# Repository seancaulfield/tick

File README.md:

tick
====

Terribly Illuminated Chronology Keeper

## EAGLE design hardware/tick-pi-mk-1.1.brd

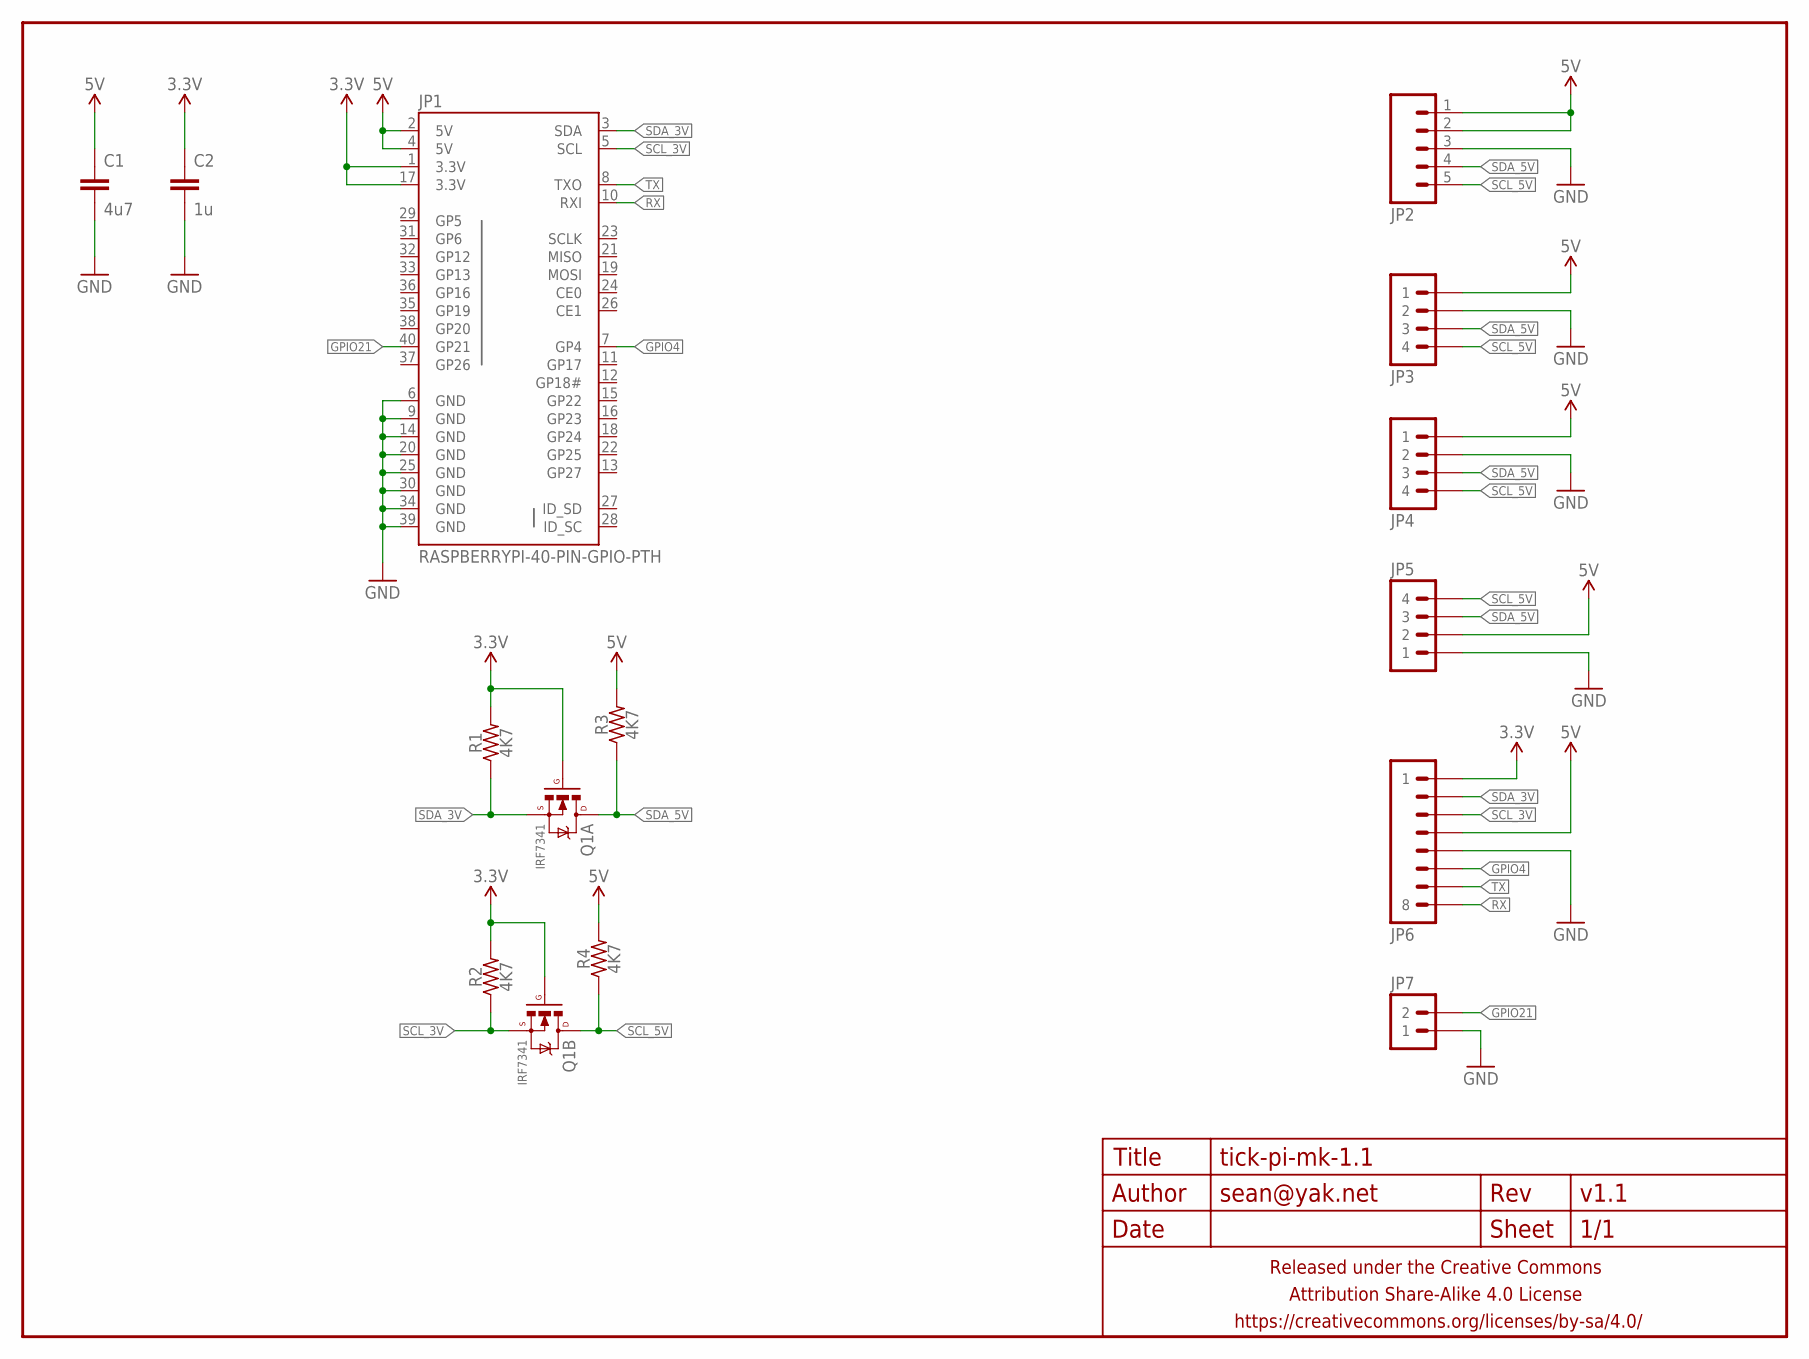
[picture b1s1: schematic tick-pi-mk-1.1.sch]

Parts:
C1: 4u7; C0805-TIGHTER
C2: 1u; C0603-TIGHTER
FRAME1: FRAME-LETTERNO_PACKAGE; DUMMY
JP1: RASPBERRYPI-40-PIN-GPIO-PTH; 2X20_PTH
JP2: M05PTH-CENTERED-RA-FEMALE; 1X05_PTH_CENTERED_RA_FEMALE
JP3, JP4, JP5: M04PTH; 1X04-PTH-VERT
JP6: M081X08; 1X08
JP7: M02PTH-CENTERED; 1X02-CENTER
Q1: IRF7341; SO08
R1, R2, R3, R4: 4K7; R0603

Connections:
3.3V: C2.1, JP1.1 (3.3V), JP1.17 (3.3V), JP6.1, Q1.2 (G), Q1.4 (G), R1.2, R2.2
5V: C1.1, JP1.2 (5V), JP1.4 (5V), JP2.1, JP2.2, JP3.1, JP4.1, JP5.2, JP6.4, R3.2, R4.2
GND: C1.2, C2.2, JP1.6 (GND), JP1.9 (GND), JP1.14 (GND), JP1.20 (GND), JP1.25 (GND), JP1.30 (GND), JP1.34 (GND), JP1.39 (GND), JP2.3, JP3.2, JP4.2, JP5.1, JP6.5, JP7.1
GPIO4: JP1.7 (GP4), JP6.6
GPIO21: JP1.40 (GP21), JP7.2
RX: JP1.10 (RXI), JP6.8
SCL_3V: JP1.5 (SCL), JP6.3, Q1.3 (S), R2.1
SCL_5V: JP2.5, JP3.4, JP4.4, JP5.4, Q1.5 (D), Q1.6 (D), R4.1
SDA_3V: JP1.3 (SDA), JP6.2, Q1.1 (S), R1.1
SDA_5V: JP2.4, JP3.3, JP4.3, JP5.3, Q1.7 (D), Q1.8 (D), R3.1
TX: JP1.8 (TXO), JP6.7

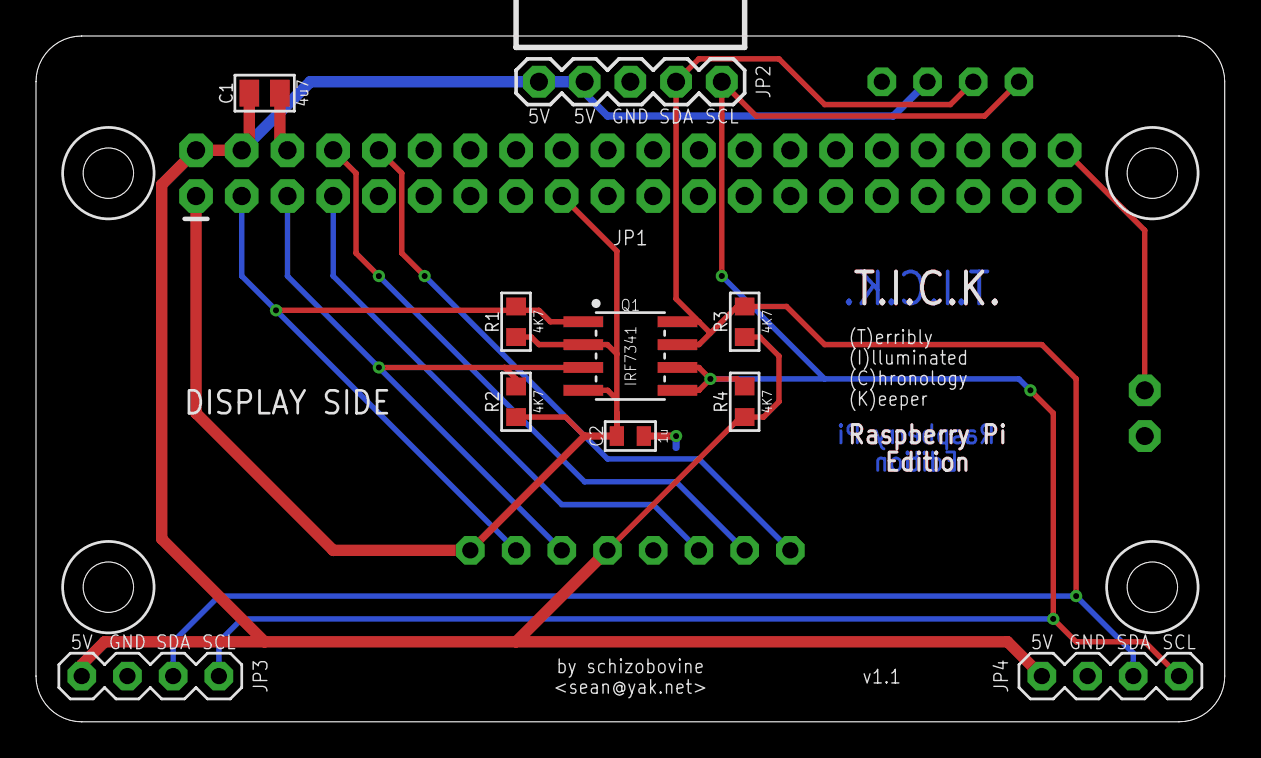
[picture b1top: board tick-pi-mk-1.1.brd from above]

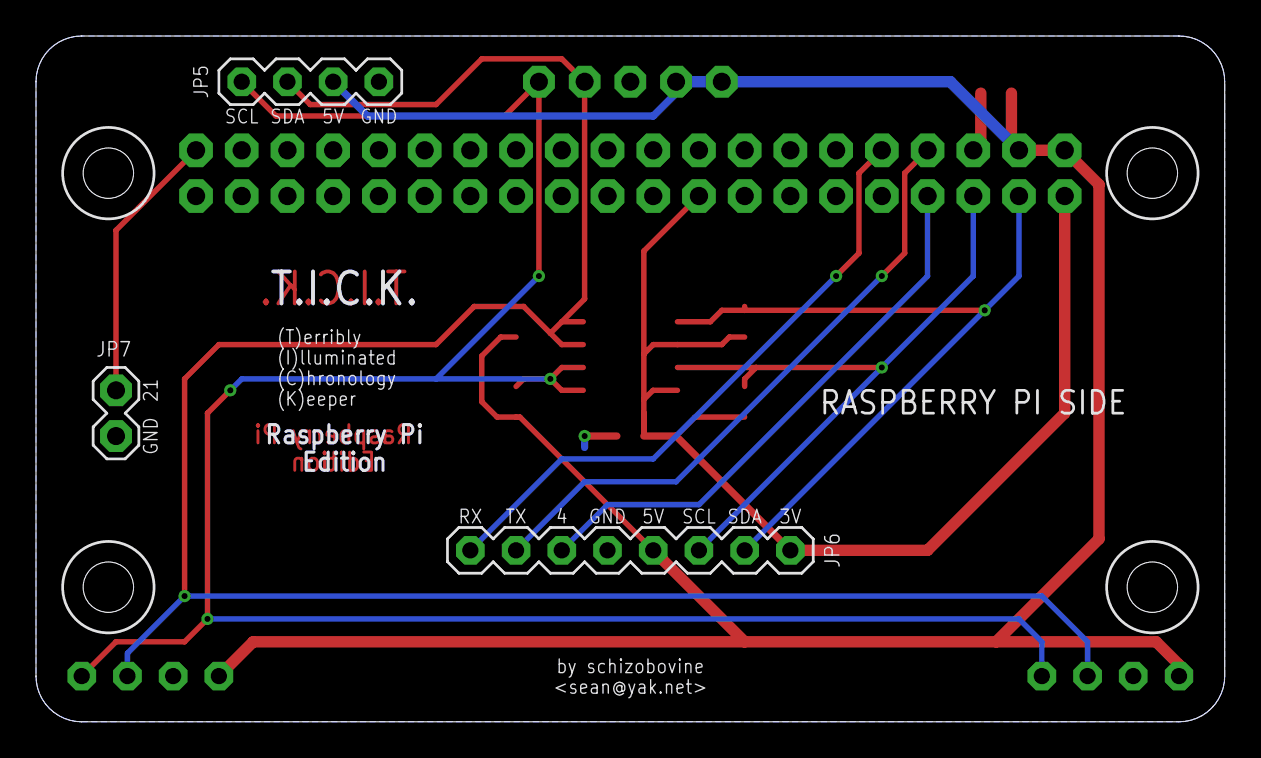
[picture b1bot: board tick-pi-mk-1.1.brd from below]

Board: 2 copper layers, 66.0 x 38.1 mm, 15 parts (3 on the bottom side), 11 nets.

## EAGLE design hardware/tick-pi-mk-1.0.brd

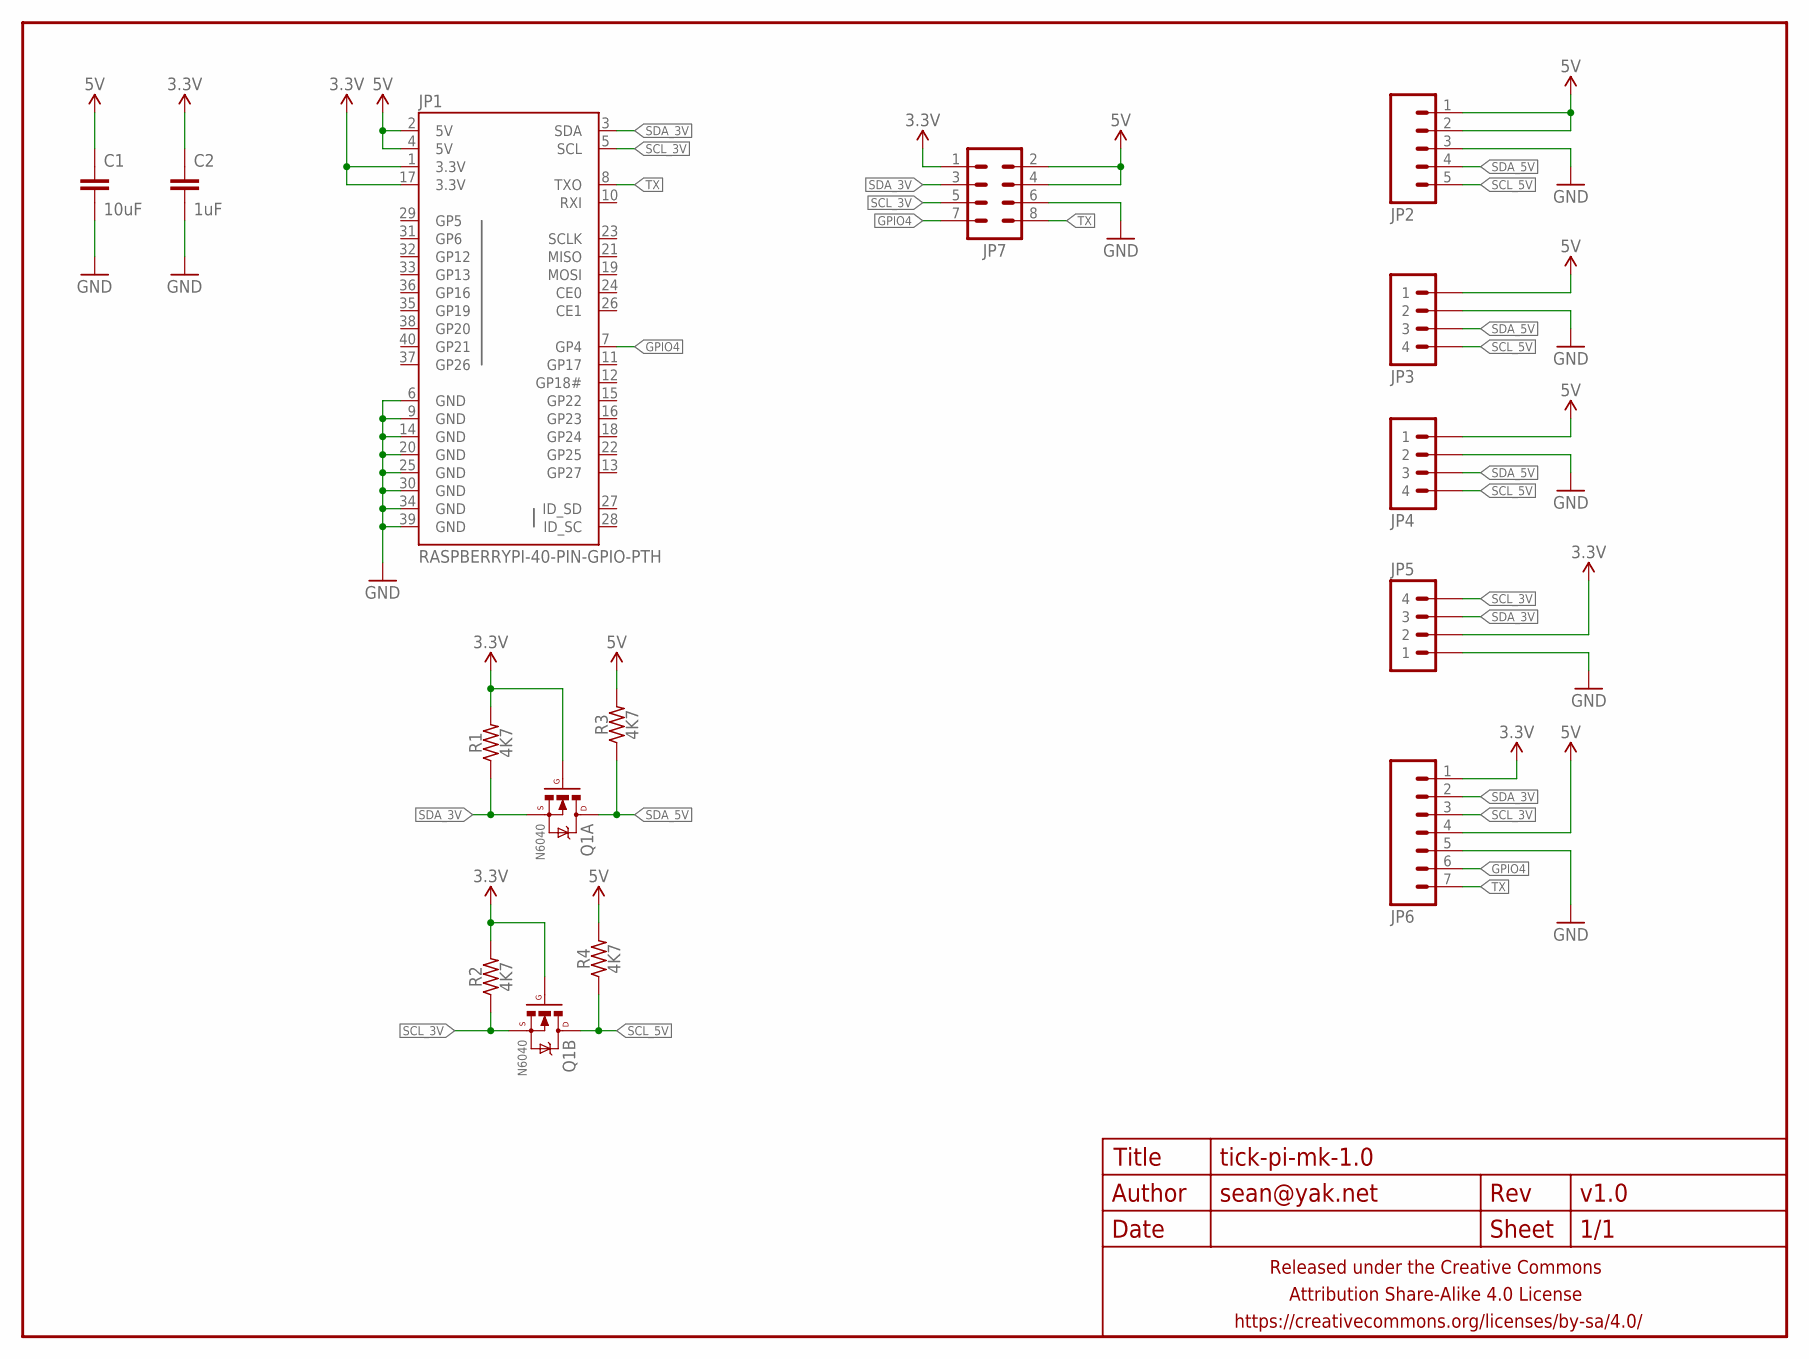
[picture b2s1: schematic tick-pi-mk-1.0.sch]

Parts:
C1: 10uF; C0805-TIGHTER
C2: 1uF; C0805-TIGHTER
FRAME1: FRAME-LETTERNO_PACKAGE; DUMMY
JP1: RASPBERRYPI-40-PIN-GPIO-PTH; 2X20_PTH
JP2: M05PTH-CENTERED-RA-FEMALE; 1X05_PTH_CENTERED_RA_FEMALE
JP3, JP4, JP5: M04PTH; 1X04-PTH-VERT
JP6: M07; 1X07
JP7: M04X2PTH; 2X4_PTH
Q1: N6040; SO08
R1, R2, R3, R4: 4K7; R0603

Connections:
3.3V: C2.1, JP1.1 (3.3V), JP1.17 (3.3V), JP5.2, JP6.1, JP7.1, Q1.2 (G), Q1.4 (G), R1.2, R2.2
5V: C1.1, JP1.2 (5V), JP1.4 (5V), JP2.1, JP2.2, JP3.1, JP4.1, JP6.4, JP7.2, JP7.4, R3.2, R4.2
GND: C1.2, C2.2, JP1.6 (GND), JP1.9 (GND), JP1.14 (GND), JP1.20 (GND), JP1.25 (GND), JP1.30 (GND), JP1.34 (GND), JP1.39 (GND), JP2.3, JP3.2, JP4.2, JP5.1, JP6.5, JP7.6
GPIO4: JP1.7 (GP4), JP6.6, JP7.7
SCL_3V: JP1.5 (SCL), JP5.4, JP6.3, JP7.5, Q1.3 (S), R2.1
SCL_5V: JP2.5, JP3.4, JP4.4, Q1.5 (D), Q1.6 (D), R4.1
SDA_3V: JP1.3 (SDA), JP5.3, JP6.2, JP7.3, Q1.1 (S), R1.1
SDA_5V: JP2.4, JP3.3, JP4.3, Q1.7 (D), Q1.8 (D), R3.1
TX: JP1.8 (TXO), JP6.7, JP7.8

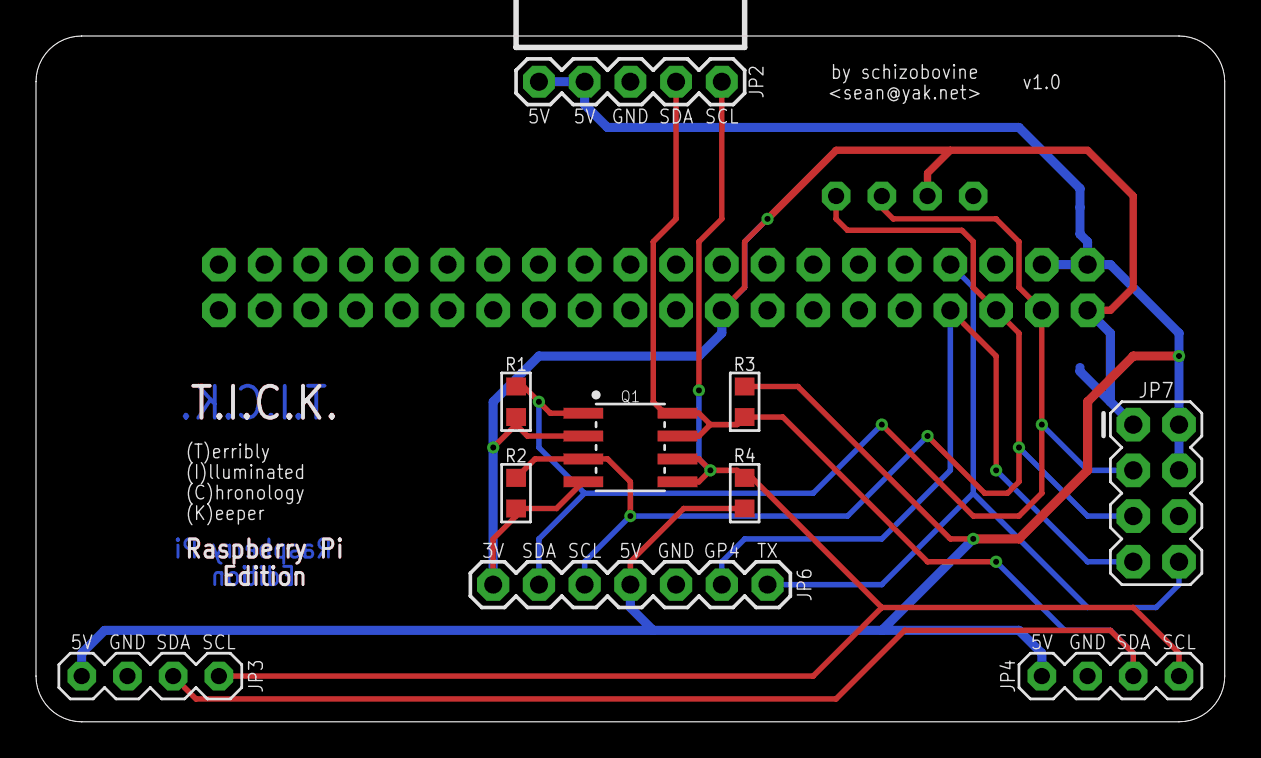
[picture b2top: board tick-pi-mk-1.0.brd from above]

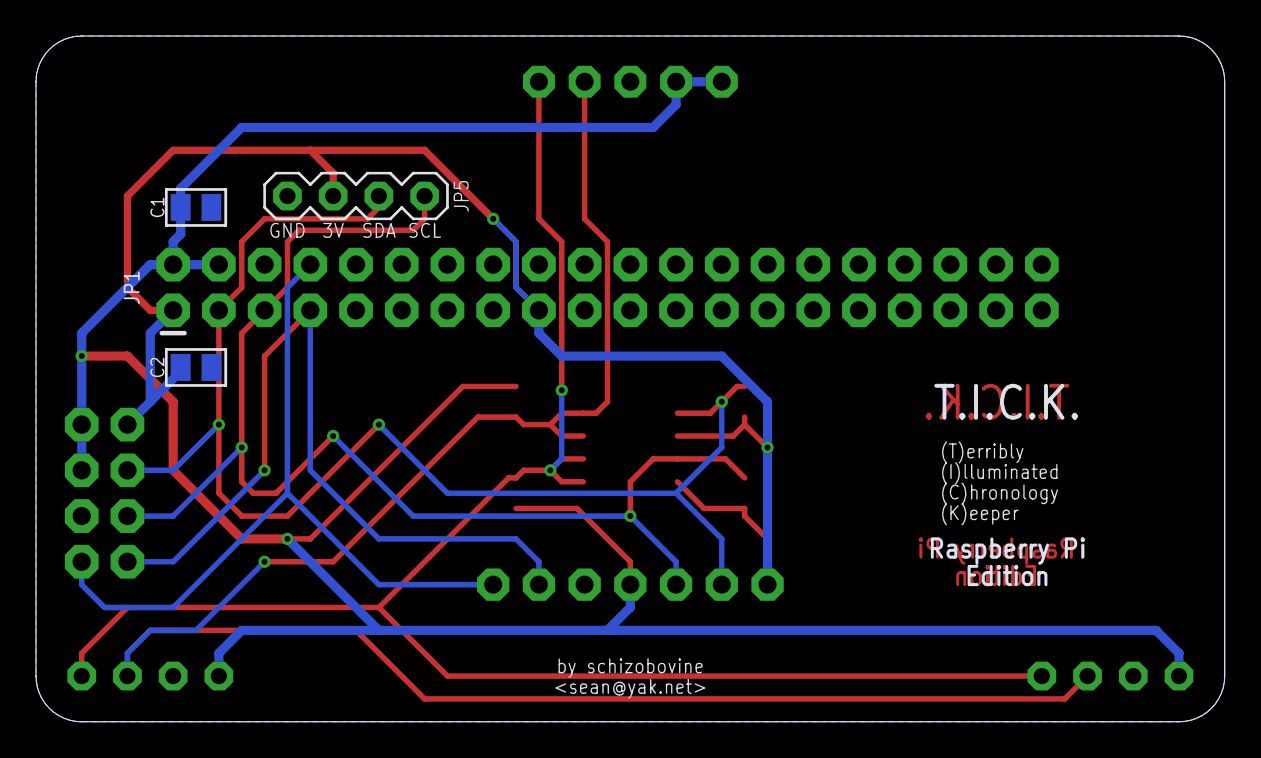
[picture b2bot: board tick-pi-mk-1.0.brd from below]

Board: 2 copper layers, 66.0 x 38.1 mm, 15 parts (4 on the bottom side), 9 nets.

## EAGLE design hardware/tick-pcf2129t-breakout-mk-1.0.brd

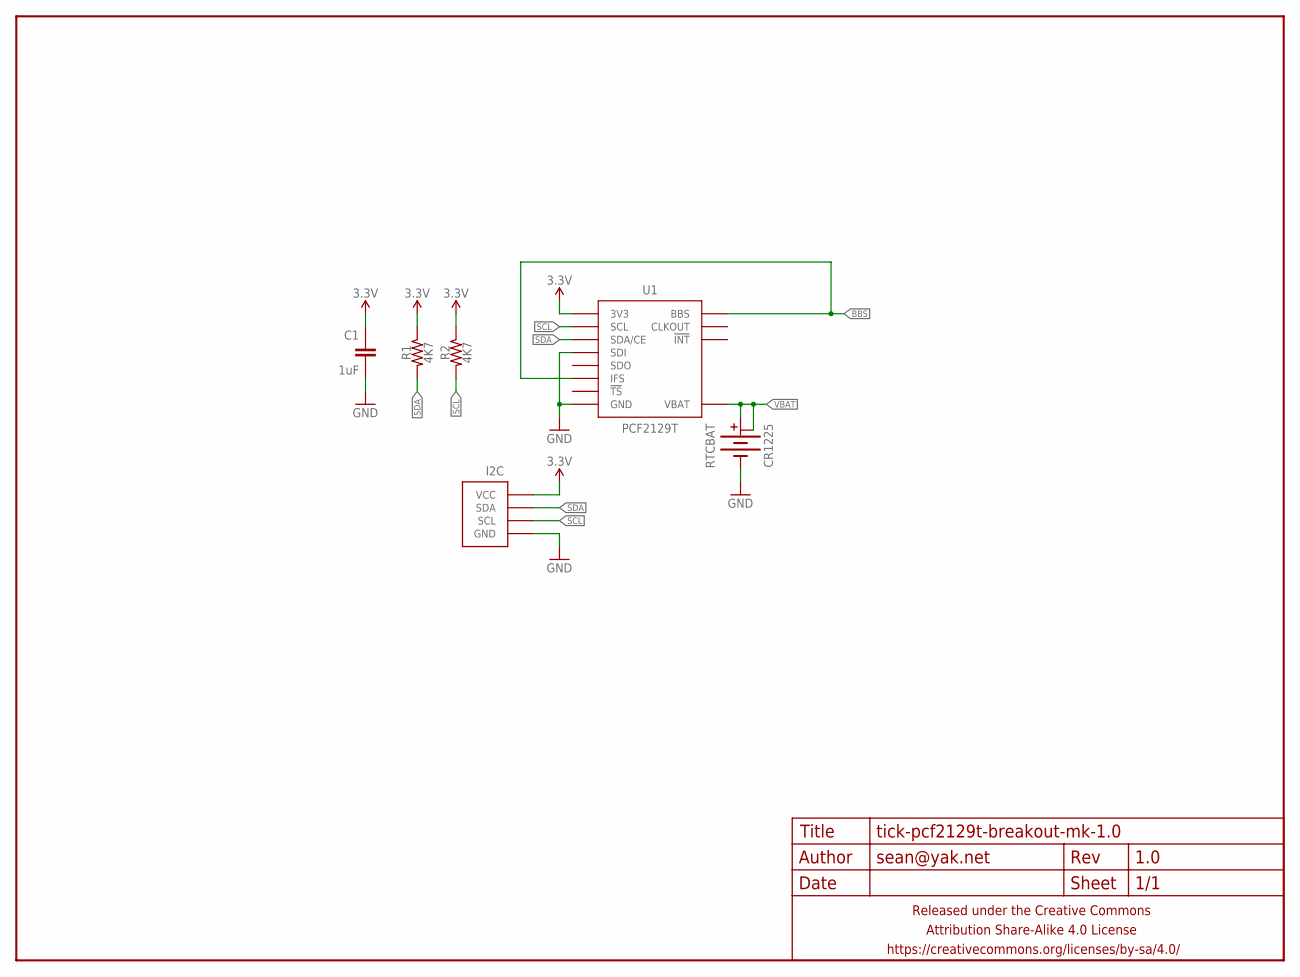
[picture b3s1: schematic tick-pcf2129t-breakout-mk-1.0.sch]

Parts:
C1: 1uF; C0603-TIGHTER
FRAME1: FRAME-LETTERNO_PACKAGE; DUMMY
I2C: M04-I2CPTH-0.1IN-CENTERED; 1X04-PTH-VERT-I2C-CENTERED
R1, R2: 4K7; R0603-TIGHTER
RTCBAT: CR1225; BATTCON_12MM_SMD
U1: PCF2129T; SO16W

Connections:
3.3V: C1.1, I2C.VCC, R1.1, R2.1, U1.16 (3V3)
BBS: U1.5 (IFS), U1.14 (BBS)
GND: C1.2, I2C.GND, RTCBAT.-, U1.2 (SDI), U1.8 (GND)
SCL: I2C.SCL, R2.2, U1.1 (SCL)
SDA: I2C.SDA, R1.2, U1.4 (SDA/CE)
VBAT: RTCBAT.+@1 (+), RTCBAT.+@2 (+1), U1.15 (VBAT)

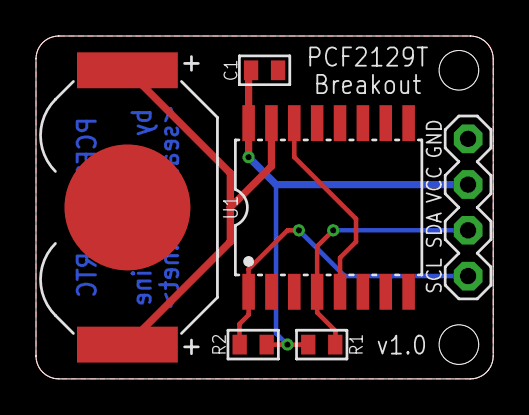
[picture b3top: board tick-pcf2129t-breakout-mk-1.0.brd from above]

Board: 2 copper layers, 25.4 x 19.1 mm, 8 parts (1 on the bottom side), 6 nets.

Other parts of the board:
U$1: COW_SMALL

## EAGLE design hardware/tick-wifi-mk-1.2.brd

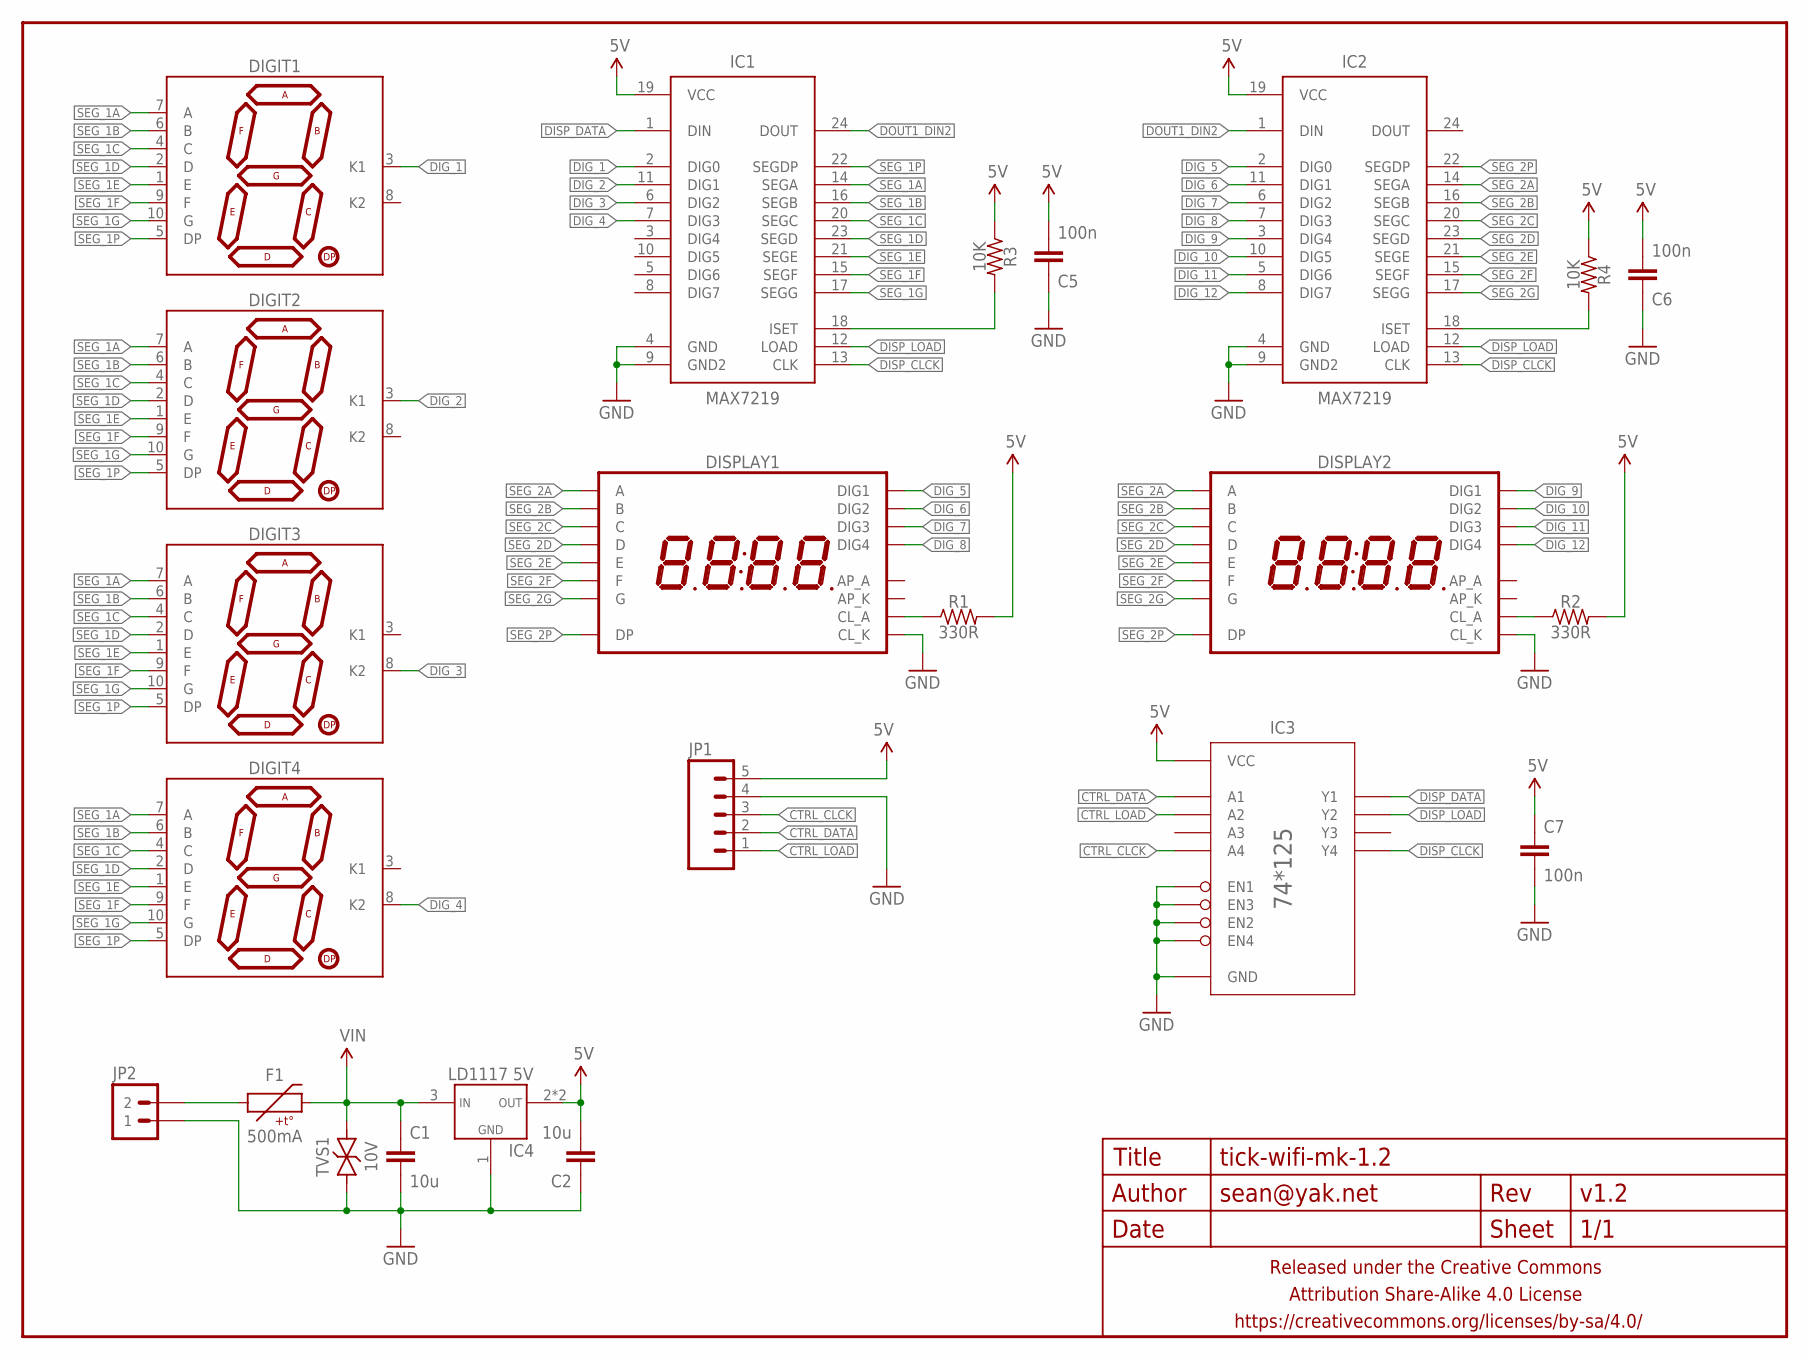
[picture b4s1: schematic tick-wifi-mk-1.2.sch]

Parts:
C1, C2: 10u; C1210
C5, C6, C7: 100n; C0603
DIGIT1, DIGIT2, DIGIT3, DIGIT4: 7SEG_1DIGPTH-25.4MM-BARE; 7SEG_1DIG_25.4MM_NOSILK
DISPLAY1, DISPLAY2: 7SEG_4DIGIT_COLON_APOS; 7SEG_4DIG_10MM
F1: 500mA; PTC-1210
FRAME1: FRAME-LETTERNO_PACKAGE; DUMMY
IC1, IC2: MAX7219; SO24W
IC3: 74HC125; SO14
IC4: LD1117 5V; SOT223
JP1: M05PTH-CENTERED; 1X05_PTH_CENTERED
JP2: M02PTH-CENTERED-R+; 1X02-CENTER-R+
R1, R2: 330R; R0603
R3, R4: 10K; R0603
TVS1: 10V; SMA-DIODE-TVS-BIDIR

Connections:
5V: C2.2, C5.2, C6.2, C7.1, IC1.19 (VCC), IC2.19 (VCC), IC3.14 (VCC), IC4.2 (VOUT), IC4.4 (VOUT), JP1.5, R1.2, R2.2, R3.1, R4.1
CTRL_CLCK: IC3.12 (A4), JP1.3
CTRL_DATA: IC3.2 (A1), JP1.2
CTRL_LOAD: IC3.5 (A2), JP1.1
DIG_1: DIGIT1.3 (K1), IC1.2 (DIG0)
DIG_2: DIGIT2.3 (K1), IC1.11 (DIG1)
DIG_3: DIGIT3.8 (K2), IC1.6 (DIG2)
DIG_4: DIGIT4.8 (K2), IC1.7 (DIG3)
DIG_5: DISPLAY1.1 (DIG1), IC2.2 (DIG0)
DIG_6: DISPLAY1.2 (DIG2), IC2.11 (DIG1)
DIG_7: DISPLAY1.6 (DIG3), IC2.6 (DIG2)
DIG_8: DISPLAY1.8 (DIG4), IC2.7 (DIG3)
DIG_9: DISPLAY2.1 (DIG1), IC2.3 (DIG4)
DIG_10: DISPLAY2.2 (DIG2), IC2.10 (DIG5)
DIG_11: DISPLAY2.6 (DIG3), IC2.5 (DIG6)
DIG_12: DISPLAY2.8 (DIG4), IC2.8 (DIG7)
DISP_CLCK: IC1.13 (CLK), IC2.13 (CLK), IC3.11 (Y4)
DISP_DATA: IC1.1 (DIN), IC3.3 (Y1)
DISP_LOAD: IC1.12 (LOAD), IC2.12 (LOAD), IC3.6 (Y2)
DOUT1_DIN2: IC1.24 (DOUT), IC2.1 (DIN)
GND: C1.2, C2.1, C5.1, C6.1, C7.2, DISPLAY1.12 (CL_K), DISPLAY2.12 (CL_K), IC1.4 (GND), IC1.9 (GND2), IC2.4 (GND), IC2.9 (GND2), IC3.1 (EN1), IC3.4 (EN2), IC3.7 (GND), IC3.10 (EN3), IC3.13 (EN4), IC4.1 (GND), JP1.4, JP2.1, TVS1.1
unnamed: F1.1, JP2.2
unnamed: IC2.18 (ISET), R4.2
unnamed: DISPLAY1.4 (CL_A), R1.1
unnamed: IC1.18 (ISET), R3.2
unnamed: DISPLAY2.4 (CL_A), R2.1
SEG_1A: DIGIT1.7 (A), DIGIT2.7 (A), DIGIT3.7 (A), DIGIT4.7 (A), IC1.14 (SEGA)
SEG_1B: DIGIT1.6 (B), DIGIT2.6 (B), DIGIT3.6 (B), DIGIT4.6 (B), IC1.16 (SEGB)
SEG_1C: DIGIT1.4 (C), DIGIT2.4 (C), DIGIT3.4 (C), DIGIT4.4 (C), IC1.20 (SEGC)
SEG_1D: DIGIT1.2 (D), DIGIT2.2 (D), DIGIT3.2 (D), DIGIT4.2 (D), IC1.23 (SEGD)
SEG_1E: DIGIT1.1 (E), DIGIT2.1 (E), DIGIT3.1 (E), DIGIT4.1 (E), IC1.21 (SEGE)
SEG_1F: DIGIT1.9 (F), DIGIT2.9 (F), DIGIT3.9 (F), DIGIT4.9 (F), IC1.15 (SEGF)
SEG_1G: DIGIT1.10 (G), DIGIT2.10 (G), DIGIT3.10 (G), DIGIT4.10 (G), IC1.17 (SEGG)
SEG_1P: DIGIT1.5 (DP), DIGIT2.5 (DP), DIGIT3.5 (DP), DIGIT4.5 (DP), IC1.22 (SEGDP)
SEG_2A: DISPLAY1.14 (A), DISPLAY2.14 (A), IC2.14 (SEGA)
SEG_2B: DISPLAY1.16 (B), DISPLAY2.16 (B), IC2.16 (SEGB)
SEG_2C: DISPLAY1.13 (C), DISPLAY2.13 (C), IC2.20 (SEGC)
SEG_2D: DISPLAY1.3 (D), DISPLAY2.3 (D), IC2.23 (SEGD)
SEG_2E: DISPLAY1.5 (E), DISPLAY2.5 (E), IC2.21 (SEGE)
SEG_2F: DISPLAY1.11 (F), DISPLAY2.11 (F), IC2.15 (SEGF)
SEG_2G: DISPLAY1.15 (G), DISPLAY2.15 (G), IC2.17 (SEGG)
SEG_2P: DISPLAY1.7 (DP), DISPLAY2.7 (DP), IC2.22 (SEGDP)
VIN: C1.1, F1.2, IC4.3 (VIN), TVS1.2

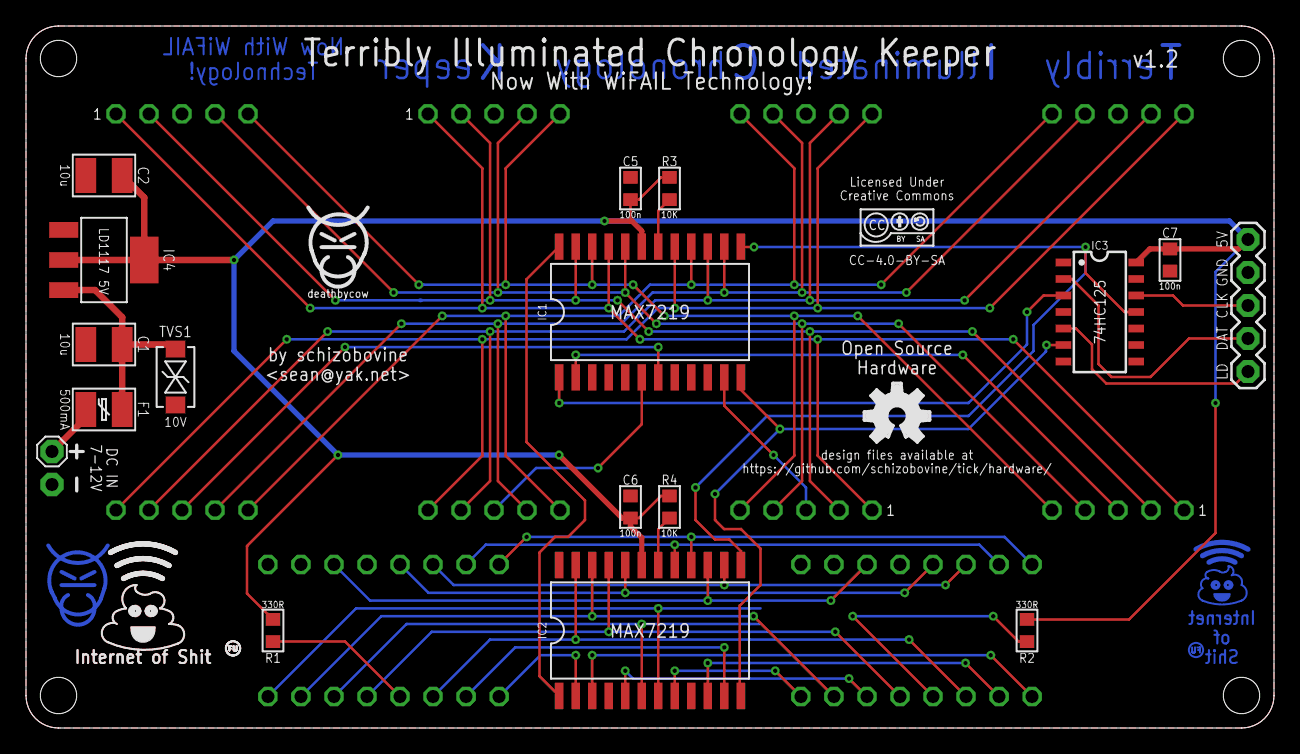
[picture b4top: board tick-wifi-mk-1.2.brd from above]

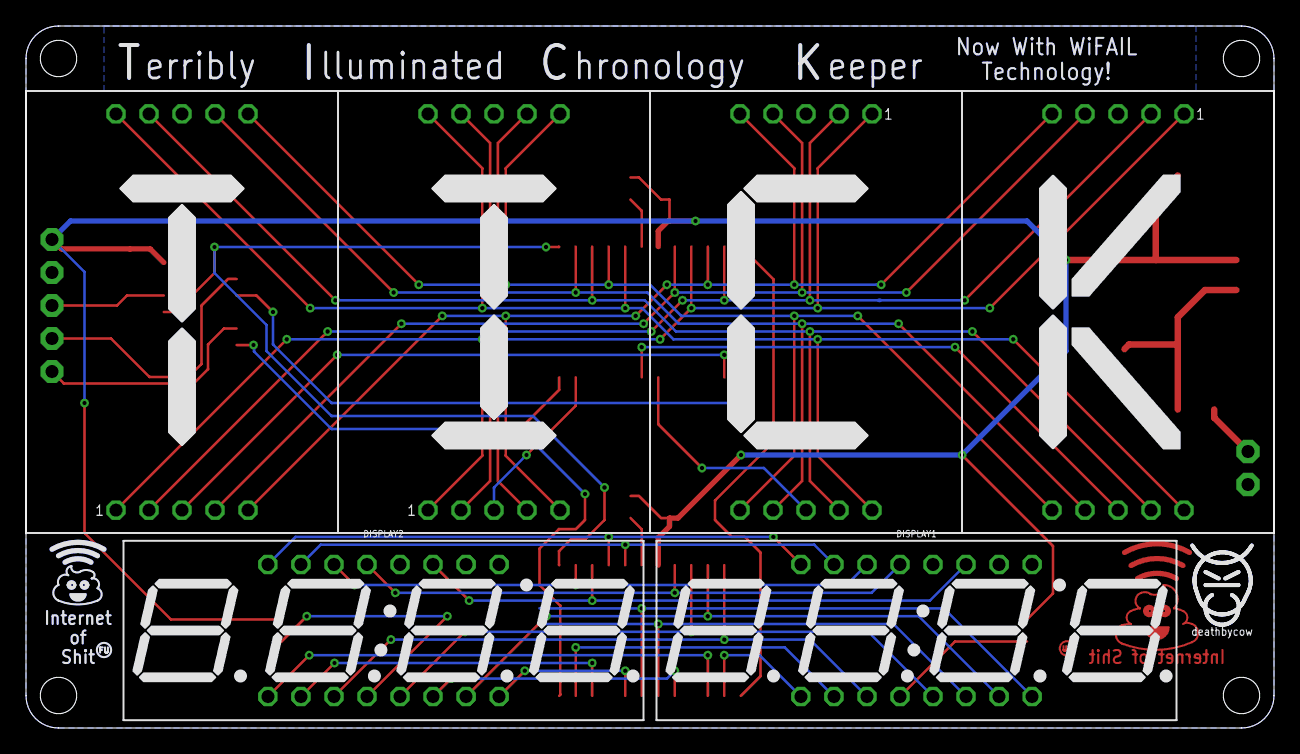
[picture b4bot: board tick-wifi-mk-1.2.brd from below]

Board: 2 copper layers, 96.0 x 54.0 mm, 34 parts (11 on the bottom side), 43 nets.

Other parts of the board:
U$1: TICK_SYMBOL
U$2, U$5: COW_SMALL
U$3: INTERNET_OF_SHIT_TEXT_METAL
U$4: INTERNET_OF_SHIT_TEXT
U$6: CC-BY-SA-4.0-NO-URL
U$7: OSHWLOGO_SILKONLY
U$8: INTERNET_OF_SHIT_JR_METAL
U$9: COW_SMALL_METAL_NOTEXT
U$10: F_YOU_MARK_METAL

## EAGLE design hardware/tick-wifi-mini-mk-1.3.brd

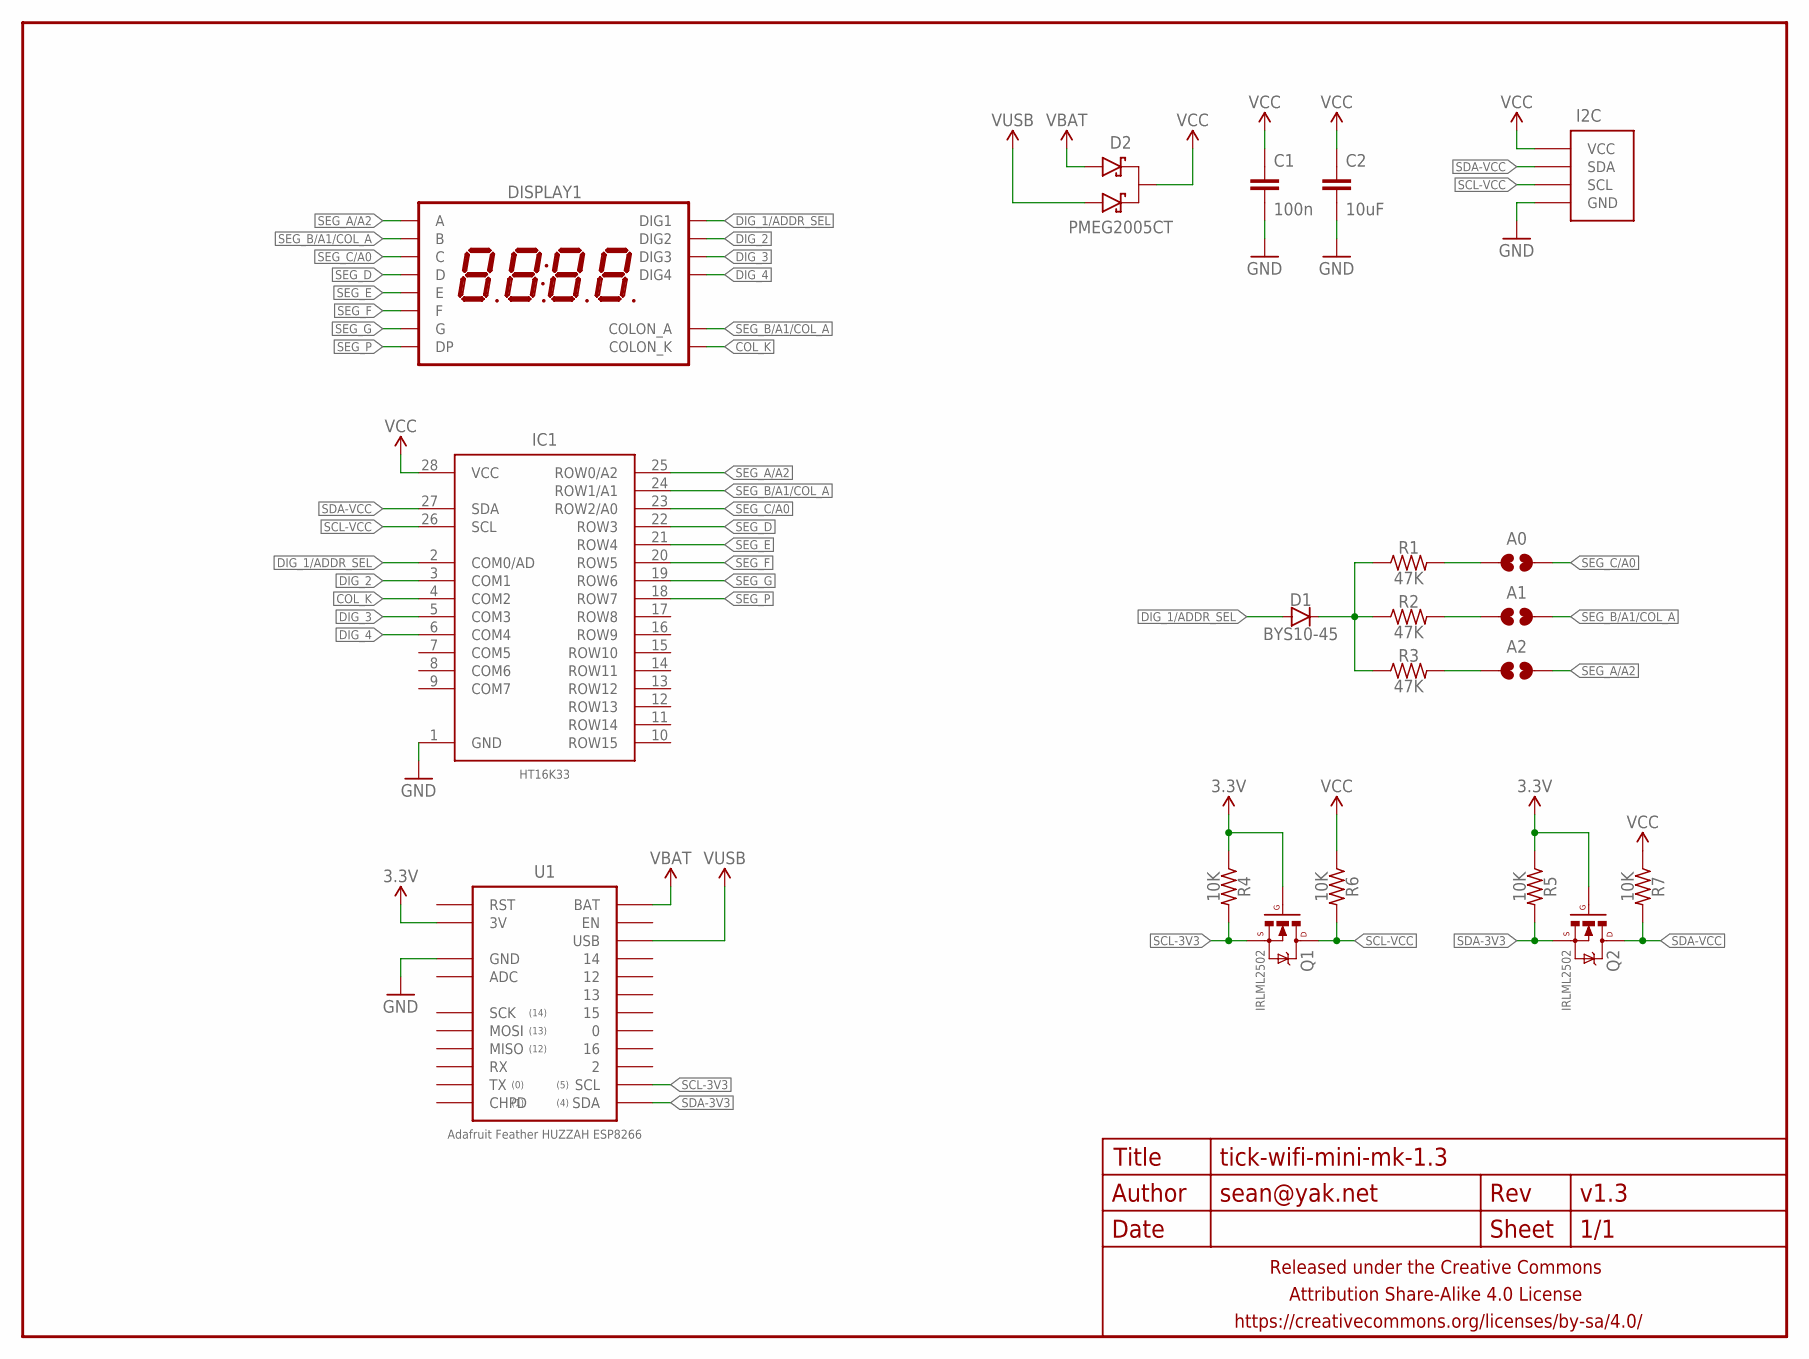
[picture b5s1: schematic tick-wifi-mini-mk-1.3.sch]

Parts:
A0, A1, A2: JUMPER-PAD-2-NOYES_SILK; PAD-JUMPER-2-NO_YES_SILK
C1: 100n; C0603-TIGHTER
C2: 10uF; C0805-TIGHTER
D1: BYS10-45; SOD323
D2: PMEG2005CT; SOT23
DISPLAY1: 7SEG_4DIGIT_COLON14.2MM-CC; 7SEG_4DIG_0.56IN_14MM_ADAFRUIT
FRAME1: FRAME-LETTERNO_PACKAGE; DUMMY
I2C: M04-I2CPTH-2MM-CENTERED; 1X04-2MM-CENTERED-I2C
IC1: HT16K33; SOIC28W
Q1, Q2: IRLML2502; SOT23
R1, R2, R3: 47K; R0603-TIGHTER
R4, R5, R6, R7: 10K; R0603-TIGHTER
U1: Adafruit Feather HUZZAH ESP8266; ADAFRUIT_FEATHER_HUZZAH_NOSILK

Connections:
3.3V: Q1.1 (G), Q2.1 (G), R4.1, R5.1, U1.3V
COL_K: DISPLAY1.P$7 (COLON_K), IC1.4 (COM2)
DIG_1/ADDR_SEL: D1.A, DISPLAY1.P$14 (DIG1), IC1.2 (COM0/AD)
DIG_2: DISPLAY1.P$11 (DIG2), IC1.3 (COM1)
DIG_3: DISPLAY1.P$10 (DIG3), IC1.5 (COM3)
DIG_4: DISPLAY1.P$6 (DIG4), IC1.6 (COM4)
GND: C1.2, C2.2, I2C.1 (GND), IC1.1 (GND), U1.GND@0 (GND)
unnamed: D1.C, R1.1, R2.1, R3.1
unnamed: A0.1, R1.2
unnamed: A1.1, R2.2
unnamed: A2.1, R3.2
SCL-3V3: Q1.2 (S), R4.2, U1.SCL
SCL-VCC: I2C.4 (SCL), IC1.26 (SCL), Q1.3 (D), R6.2
SDA-3V3: Q2.2 (S), R5.2, U1.SDA
SDA-VCC: I2C.3 (SDA), IC1.27 (SDA), Q2.3 (D), R7.2
SEG_A/A2: A2.2, DISPLAY1.P$13 (A), IC1.25 (ROW0/A2)
SEG_B/A1/COL_A: A1.2, DISPLAY1.P$8 (COLON_A), DISPLAY1.P$9 (B), IC1.24 (ROW1/A1)
SEG_C/A0: A0.2, DISPLAY1.P$4 (C), IC1.23 (ROW2/A0)
SEG_D: DISPLAY1.P$2 (D), IC1.22 (ROW3)
SEG_E: DISPLAY1.P$1 (E), IC1.21 (ROW4)
SEG_F: DISPLAY1.P$12 (F), IC1.20 (ROW5)
SEG_G: DISPLAY1.P$5 (G), IC1.19 (ROW6)
SEG_P: DISPLAY1.P$3 (DP), IC1.18 (ROW7)
VBAT: D2.1 (A1), U1.BAT
VCC: C1.1, C2.1, D2.3 (K), I2C.2 (VCC), IC1.28 (VCC), R6.1, R7.1
VUSB: D2.2 (A2), U1.USB

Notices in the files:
hardware/tick-wifi-mk-1.2.brd:
Licensed Under
Creative Commons
parts and their libraries:
A_butts: Released under the Creative Commons Attribution Share-Alike 4.0 License
A_butts: https://creativecommons.org/licenses/by-sa/4.0
A_butts: Released under the Creative Commons
